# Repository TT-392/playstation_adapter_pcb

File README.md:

# RP2040 PlayStation adapter
This project is a simple PlayStation 1/2 controller port to USB C adapter. I made it so that I would be able to use it with the cheap, second hand, PlayStation 2, Taiko no Tatsujin drum, which I bought while in Japan.

I only wrote software for the Taiko drum, but in theory, all of the hardware is there to support a lot of different kinds of PlayStation controllers. The firmware can be found [here](https://github.com/TT-392/playstation_adapter_code).

## Using the hardware with non Taiko drum controllers
If you want to use this hardware with other PlayStation controllers, you are going to have to write your own firmware. For details on how to do this, I recommend the following source: [Interfacing a PS2 (PlayStation 2) Controller](https://store.curiousinventor.com/guides/PS2/).

One thing to keep in mind is power requirements of the controller you are using. I haven't found much information on how much power controllers pull (not that I put in that much effort), except for what is mentioned in the aforementioned source. Therefore, I can only give information on the power supply situation of this PCB.
* Pin 5 (power). This pin gets 3.3V through an AMS1117-3.3 voltage regulator. This voltage regulator is rated for 1A (though, this does assume that it is able to get rid of the heat), but that does assume that your USB port is able to supply that. Therefore, its power rating is, whatever your USB port is able to deliver if that is < 1A, otherwise 1A.
* Pin 3 (vibrator power). This pin is connected to the USB port VBUS pin (5V) through a 0 ohm resistor, so it can be enabled or disabled by placing or not placing that resistor. I don't know how this pin is usually used, because I only have a Taiko drum, and that drum doesn't have a vibration motor, but it felt like a good idea to give the option to leave it unconnected in case there exists a controller which pulls too much power for a USB port with the vibration motor powered, but not without it powered (assuming the controller would even work like that).
* I referred to USB power in those last 2 points. This table on [Wikipedia](https://en.wikipedia.org/wiki/USB#Power) should help you in figuring out what that is. Keep in mind that the type-c power delivery standards need extra communication between your device and the supply, and therefore cannot be used in this case. While with the BC 1.1 and 1.2 specs, you are supposed to check if there is a resistor between the D+ and D- lines to check if you are allowed to pull that much power, this PCB doesn't have the hardware to check that, but (although it is probably a bad idea), nothing is stopping you from pulling that much from ports capable of this.

## Ordering
I used JLCPCB to order my PCBs with all of their parts already pick and placed. I used [this](https://github.com/Bouni/kicad-jlcpcb-tools) plugin to do this. However, if you just want to order the same PCBs as I did, without any modifications, you can just grab the production files from the "JLCPCB" folder, or from the "releases" tab on github. The rest of this guide assumes you have your PCBs with the SMD components fully assembled at JLCPCB (nothing is stopping you from soldering them on yourself of course).

Apart from the PCBs, you should get your hands on some PlayStation controller ports with 90 degree pins. I got mine from [AliExpress](https://www.aliexpress.com/item/32818887920.html?spm=a2g0o.order_list.order_list_main.17.45ed1802iEjUwq) (AliExpress links rot quickly, but you should be able to find something similar). And some 9 pin, 3.96mm pitch pin header, I used [these](https://www.lcsc.com/product-detail/_BOOMELE-Boom-Precision-Elec-_C10586.html) (At the time of writing, you get free shipping on LCSC, if your recently ordered something from JLCPCB). And if you want some protection for your board, get some 50mm diameter heat-shrink (I got [this](https://www.aliexpress.com/item/1005002849810793.html?spm=a2g0o.order_detail.order_detail_item.3.59a3f19cWbd98H) stuff from AliExpress, seems to work well).

## assembly
If you followed the ordering instructions, you should now have a PCB that looks something like one of these:

Because the 90 degree PlayStation ports don't quite reach to the PCB, a we need something to bridge the gap. To do this, I decided to use some 3.96mm pitch, 9 pin pin headers, sadly, I couldn't find any without a plastic tab, so I just got the ones that looked like they had a tab that was easy to remove. So that is the first step in assembly, remove this tab, like is shown in the following image:

Next, this header should be soldered to the PCB, I have found that it works best if you solder on the connector with the pins sticking out about 5 mm, and with the side of the connector that has the least plastic, pointing to the edge of the board, to allow for easier snipping later (I found out about this orientation trick in the next one I assembled, therefore the pictures have the connector rotated by 180 degrees compared to what I am saying here).

Next, we glue (I used hot glue) the connector to the bottom side of the PCB, with the pins as close as possible to the pin header's pins, like shown in the following picture

The next step is to solder these pins together, be sure to use ample solder, to make sure the pins really have a good connection.

After you have soldered these pins together, you can go ahead and use some side cutters to cut the pins of the connector on the other side of the board. The result of these two steps can be seen in the following image:

Now it is time to heat shrink our adapter for some extra protection. Cut off a decent size piece of the heat shrink, so that the adapter can sit inside, with ample space on both sides:

Now use a heat gun to shrink the heat-shrink:

Now we can cut away the excess heat-shrink (I used normal scissors, just make sure they are scissors that close well), and we have our finished adapter:

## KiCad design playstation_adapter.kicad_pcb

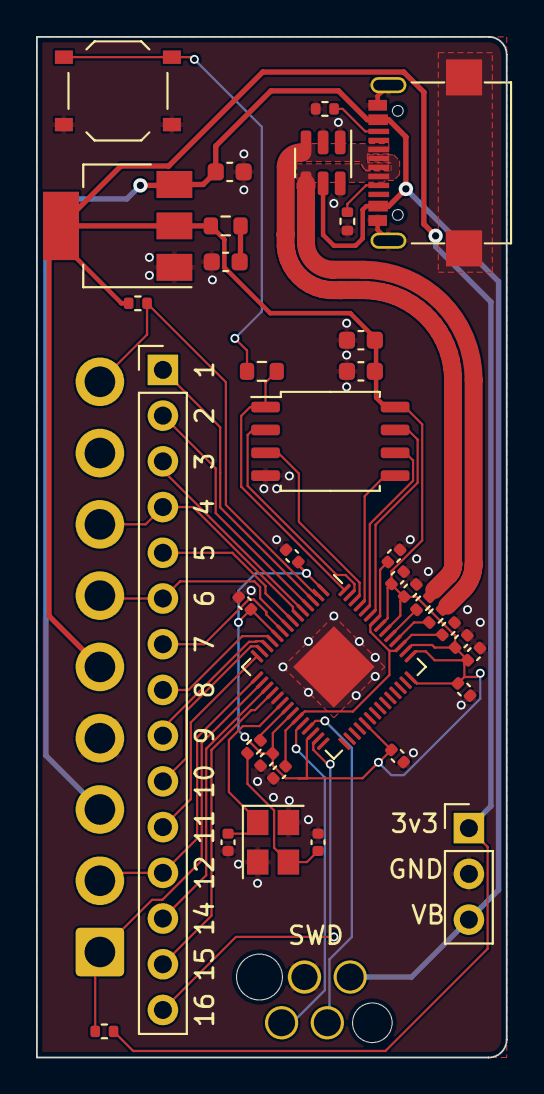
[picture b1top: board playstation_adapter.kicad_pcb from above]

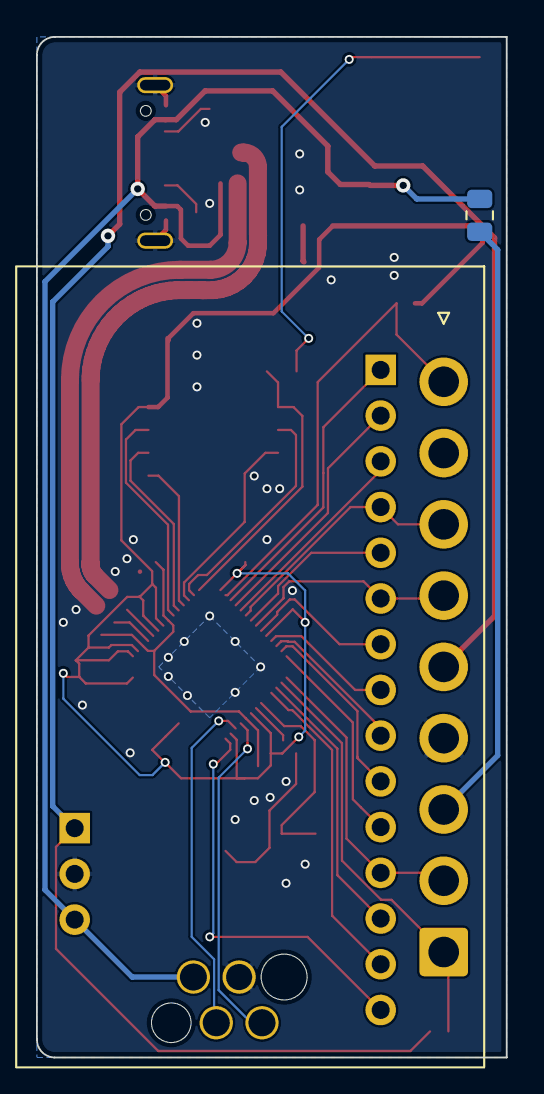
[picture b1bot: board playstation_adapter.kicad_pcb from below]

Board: 2 copper layers, 26.1 x 56.7 mm, 39 parts (2 on the bottom side), 41 nets.

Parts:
C1: 1u; C_0603_1608Metric
C2: 22u; C_0603_1608Metric
C3, C4, C5, C6, C7, C8, C9, C10, C11, C12: 100n; C_0402_1005Metric
C13, C14: 1u; C_0402_1005Metric
C15, C16: 30p; C_0402_1005Metric
C17: 100n; C_0603_1608Metric
C18: 10n; C_0603_1608Metric
J1: Conn_01x03; PinHeader_1x03_P2.54mm_Vertical
J2: Conn_01x13; PinHeader_1x15_P2.54mm_Vertical_no_courtyard
J3: GT-USB-7047C
J4: PSX port
R1: 1R; R_0603_1608Metric
R2: 0, DNF; R_0805_2012Metric
R3, R4: 27; R_0402_1005Metric
R5: 1k; R_0402_1005Metric
R6: 1k; R_0603_1608Metric
R7, R8: 5k1; R_0402_1005Metric
R9, R10: 1k5; R_0402_1005Metric
SW1: SW_Push; TS-1187A
SWD1: Conn_01x04; REDFIT 4 pin
U1: AMS1117-3.3; SOT-223-3_TabPin2_flipped_for_jlcpcb
U2: SRV05-4; SOT-23-6_flipped_for_jlcpcb
U3: RP2040; QFN-56-1EP_7x7mm_P0.4mm_EP3.2x3.2mm
U4: W25QXXXJV; SOIC-8_5.275x5.275mm_P1.27mm
Y1: X322512MSB4SI; YSX321SL, datasheet recommended measurements

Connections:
+3V3: C5.1, C6.1, C7.1, C8.1, C9.1, C10.1, C11.1, C12.1, C14.1, C17.1, C18.1, J1.1, J4.5 (pwr), R1.1, R9.1, R10.1, U1.2 (VO), U3.1 (IOVDD), U3.10 (IOVDD), U3.22 (IOVDD), U3.26 (RUN), U3.33 (IOVDD), U3.42 (IOVDD), U3.43 (ADC_AVDD), U3.44 (VREG_IN), U3.48 (USB_VDD), U3.49 (IOVDD), U4.8 (VCC)
/RP2040-base/1V1: C3.1, C4.1, C13.1, U3.23 (DVDD), U3.45 (VREG_VOUT), U3.50 (DVDD)
/RP2040-base/GPIO0: J4.9 (ack), R10.2, U3.2 (GPIO0)
/RP2040-base/GPIO1: J2.1, U3.3 (GPIO1)
/RP2040-base/GPIO2: J2.2, U3.4 (GPIO2)
/RP2040-base/GPIO3: J2.3, U3.5 (GPIO3)
/RP2040-base/GPIO4: J2.4, J4.7 (clk), U3.6 (GPIO4)
/RP2040-base/GPIO5: J2.5, U3.7 (GPIO5)
/RP2040-base/GPIO6: J2.6, J4.6 (att), U3.8 (GPIO6)
/RP2040-base/GPIO7: J2.7, U3.9 (GPIO7)
/RP2040-base/GPIO8: J2.8, U3.11 (GPIO8)
/RP2040-base/GPIO9: J2.9, U3.12 (GPIO9)
/RP2040-base/GPIO10: J2.10, U3.13 (GPIO10)
/RP2040-base/GPIO11: J2.11, U3.14 (GPIO11)
/RP2040-base/GPIO12: J2.12, J4.2 (cmd), U3.15 (GPIO12)
/RP2040-base/GPIO13: J4.1 (data), R9.2, U3.16 (GPIO13)
/RP2040-base/GPIO14: J2.13, U3.17 (GPIO14)
/RP2040-base/GPIO15: J2.14, U3.18 (GPIO15)
/RP2040-base/GPIO16: J2.15, U3.27 (GPIO16)
/RP2040-base/QSPI_SCLK: U3.52 (QSPI_SCLK), U4.6 (CLK)
/RP2040-base/QSPI_SD0: U3.53 (QSPI_SD0), U4.5 (DI(IO0))
/RP2040-base/QSPI_SD1: U3.55 (QSPI_SD1), U4.2 (DO(IO1))
/RP2040-base/QSPI_SD2: U3.54 (QSPI_SD2), U4.3 (IO2)
/RP2040-base/QSPI_SD3: U3.51 (QSPI_SD3), U4.7 (IO3)
/RP2040-base/QSPI_SS: R6.1, U3.56 (QSPI_SS), U4.1 (~CS)
/RP2040-base/SWCLK: SWD1.1, U3.24 (SWCLK)
/RP2040-base/SWD: SWD1.3, U3.25 (SWD)
/RP2040-base/USB_D+: J3.A6 (D+), J3.B6 (D+), R3.1, U2.3 (IO2)
/RP2040-base/USB_D-: J3.A7 (D-), J3.B7 (D-), R4.1, U2.4 (IO3)
/RP2040-base/XIN: C15.1, U3.20 (XIN), Y1.1
/RP2040-base/XOUT: R5.1, U3.21 (XOUT)
/RP2040-base/~USB_BOOT: R6.2, SW1.2
/vibrator power: J4.3 (vpwr), R2.2
GND: C1.2, C2.2, C3.2, C4.2, C5.2, C6.2, C7.2, C8.2, C9.2, C10.2, C11.2, C12.2, C13.2, C14.2, C15.2, C16.2, C17.2, C18.2, J1.2, J3.A1 (GND), J3.A12 (GND), J3.B1 (GND), J3.B12 (GND), J3.S1 (SHIELD), J4.4 (gnd), R7.2, R8.2, SW1.1, SWD1.2, U1.1 (GND), U2.1 (IO1), U2.2 (VN), U2.6 (IO4), U3.19 (TESTEN), U3.57 (GND), U4.4 (GND), Y1.2, Y1.4
unnamed: C2.1, R1.2
unnamed: C16.1, R5.2, Y1.3
unnamed: J3.A5 (CC1), R7.1
unnamed: J3.B5 (CC2), R8.1
unnamed: R4.2, U3.46 (USB_DM)
unnamed: R3.2, U3.47 (USB_DP)
VBUS: C1.1, J1.3, J3.A4 (VBUS), J3.A9 (VBUS), J3.B4 (VBUS), J3.B9 (VBUS), R2.1, SWD1.4, U1.3 (VI), U2.5 (VP)

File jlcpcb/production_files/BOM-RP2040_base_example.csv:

Comment,Designator,Footprint,LCSC
1k,R5,R_0402_1005Metric,C11702
100n,C17,C_0603_1608Metric,C14663
100n,"C10,C11,C12,C3,C4,C5,C6,C7,C8,C9",C_0402_1005Metric,C1525
30p,"C15,C16",C_0402_1005Metric,C1570
1u,"C1,C2",C_0603_1608Metric,C15849
RP2040,U3,QFN-56-1EP_7x7mm_P0.4mm_EP3.2x3.2mm,C2040
1k,R6,R_0603_1608Metric,C21190
27,"R3,R4",R_0402_1005Metric,C25092
5k1,"R1,R2",R_0402_1005Metric,C25905
SW_Push,SW1,TS-1187A,C318884
1u,"C13,C14",C_0402_1005Metric,C52923
XC6206P332MR,U1,SOT-23-3_flipped_for_jlcpcb,C5446
10n,C18,C_0603_1608Metric,C57112
SRV05-4,U2,SOT-23-6_flipped_for_jlcpcb,C85364
X322512MSB4SI,Y1,"YSX321SL, datasheet recommended measurements",C9002
GT-USB-7047C,J3,GT-USB-7047C,C963218
W25QXXXJV,U4,SOIC-8_5.275x5.275mm_P1.27mm,C97521
Conn_01x03,J1,PinHeader_1x03_P2.54mm_Vertical,
Conn_01x03,SWD1,PinHeader_1x03_P2.54mm_Vertical,
Conn_01x13,J2,PinHeader_1x13_P2.54mm_Vertical,

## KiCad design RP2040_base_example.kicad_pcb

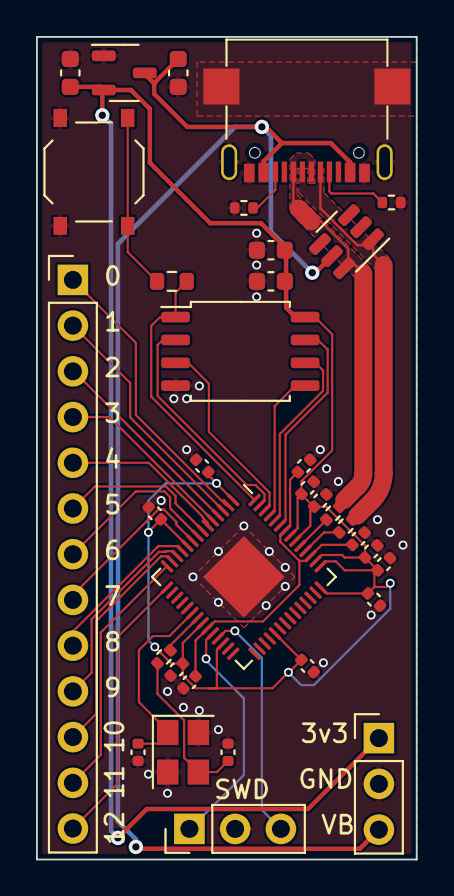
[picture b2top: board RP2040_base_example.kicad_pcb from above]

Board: 2 copper layers, 21.1 x 45.7 mm, 34 parts (0 on the bottom side), 35 nets.

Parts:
C1, C2: 1u; C_0603_1608Metric
C3, C4, C5, C6, C7, C8, C9, C10, C11, C12: 100n; C_0402_1005Metric
C13, C14: 1u; C_0402_1005Metric
C15, C16: 30p; C_0402_1005Metric
C17: 100n; C_0603_1608Metric
C18: 10n; C_0603_1608Metric
J1: Conn_01x03; PinHeader_1x03_P2.54mm_Vertical
J2: Conn_01x13; PinHeader_1x13_P2.54mm_Vertical
J3: GT-USB-7047C
R1, R2: 5k1; R_0402_1005Metric
R3, R4: 27; R_0402_1005Metric
R5: 1k; R_0402_1005Metric
R6: 1k; R_0603_1608Metric
SW1: SW_Push; TS-1187A
SWD1: Conn_01x03; PinHeader_1x03_P2.54mm_Vertical
U1: XC6206P332MR; SOT-23-3_flipped_for_jlcpcb
U2: SRV05-4; SOT-23-6_flipped_for_jlcpcb
U3: RP2040; QFN-56-1EP_7x7mm_P0.4mm_EP3.2x3.2mm
Ur: W25QXXXJV; SOIC-8_5.275x5.275mm_P1.27mm
Y1: X322512MSB4SI; YSX321SL, datasheet recommended measurements

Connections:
+3V3: C2.1, C5.1, C6.1, C7.1, C8.1, C9.1, C10.1, C11.1, C12.1, C14.1, C17.1, C18.1, J1.1, U1.2 (VO), U3.1 (IOVDD), U3.10 (IOVDD), U3.22 (IOVDD), U3.26 (RUN), U3.33 (IOVDD), U3.42 (IOVDD), U3.43 (ADC_AVDD), U3.44 (VREG_IN), U3.48 (USB_VDD), U3.49 (IOVDD), Ur.8 (VCC)
/RP2040-base/1V1: C3.1, C4.1, C13.1, U3.23 (DVDD), U3.45 (VREG_VOUT), U3.50 (DVDD)
/RP2040-base/GPIO0: J2.1, U3.2 (GPIO0)
/RP2040-base/GPIO1: J2.2, U3.3 (GPIO1)
/RP2040-base/GPIO2: J2.3, U3.4 (GPIO2)
/RP2040-base/GPIO3: J2.4, U3.5 (GPIO3)
/RP2040-base/GPIO4: J2.5, U3.6 (GPIO4)
/RP2040-base/GPIO5: J2.6, U3.7 (GPIO5)
/RP2040-base/GPIO6: J2.7, U3.8 (GPIO6)
/RP2040-base/GPIO7: J2.8, U3.9 (GPIO7)
/RP2040-base/GPIO8: J2.9, U3.11 (GPIO8)
/RP2040-base/GPIO9: J2.10, U3.12 (GPIO9)
/RP2040-base/GPIO10: J2.11, U3.13 (GPIO10)
/RP2040-base/GPIO11: J2.12, U3.14 (GPIO11)
/RP2040-base/GPIO12: J2.13, U3.15 (GPIO12)
/RP2040-base/QSPI_SCLK: U3.52 (QSPI_SCLK), Ur.6 (CLK)
/RP2040-base/QSPI_SD0: U3.53 (QSPI_SD0), Ur.5 (DI(IO0))
/RP2040-base/QSPI_SD1: U3.55 (QSPI_SD1), Ur.2 (DO(IO1))
/RP2040-base/QSPI_SD2: U3.54 (QSPI_SD2), Ur.3 (IO2)
/RP2040-base/QSPI_SD3: U3.51 (QSPI_SD3), Ur.7 (IO3)
/RP2040-base/QSPI_SS: R6.1, U3.56 (QSPI_SS), Ur.1 (~CS)
/RP2040-base/SWCLK: SWD1.1, U3.24 (SWCLK)
/RP2040-base/SWD: SWD1.3, U3.25 (SWD)
/RP2040-base/USB_D+: J3.A6 (D+), J3.B6 (D+), R3.1, U2.6 (IO4)
/RP2040-base/USB_D-: J3.A7 (D-), J3.B7 (D-), R4.1, U2.1 (IO1)
/RP2040-base/XIN: C15.1, U3.20 (XIN), Y1.1
/RP2040-base/XOUT: R5.1, U3.21 (XOUT)
/RP2040-base/~USB_BOOT: R6.2, SW1.2
GND: C1.2, C2.2, C3.2, C4.2, C5.2, C6.2, C7.2, C8.2, C9.2, C10.2, C11.2, C12.2, C13.2, C14.2, C15.2, C16.2, C17.2, C18.2, J1.2, J3.A1 (GND), J3.A12 (GND), J3.B1 (GND), J3.B12 (GND), J3.S1 (SHIELD), R1.2, R2.2, SW1.1, SWD1.2, U1.1 (GND), U2.2 (VN), U2.3 (IO2), U2.4 (IO3), U3.19 (TESTEN), U3.57 (GND), Ur.4 (GND), Y1.2, Y1.4
unnamed: C16.1, R5.2, Y1.3
unnamed: J3.A5 (CC1), R1.1
unnamed: J3.B5 (CC2), R2.1
unnamed: R4.2, U3.46 (USB_DM)
unnamed: R3.2, U3.47 (USB_DP)
VBUS: C1.1, J1.3, J3.A4 (VBUS), J3.A9 (VBUS), J3.B4 (VBUS), J3.B9 (VBUS), U1.3 (VI), U2.5 (VP)

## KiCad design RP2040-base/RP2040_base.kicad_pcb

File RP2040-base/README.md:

# RP2040-base
Basic drop in RP2040 kicad schematic sheet

# IMPORTANT
Not quite ready for use yet, for details, see notes.md.

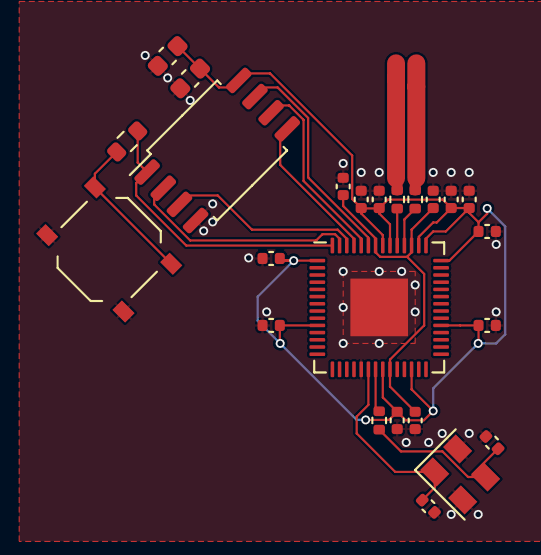
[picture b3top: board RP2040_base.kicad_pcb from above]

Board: 2 copper layers, 24 parts (0 on the bottom side), 15 nets.

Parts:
C1, C2, C3, C4, C5, C8, C9, C18, C19, C28: 100n; C_0402_1005Metric
C6, C7: 1u; C_0402_1005Metric
C29: 100n; C_0603_1608Metric
C30: 10n; C_0603_1608Metric
C31, C32: 30p; C_0402_1005Metric
R6, R7: 27; R_0402_1005Metric
R8: 1k; R_0603_1608Metric
R10: 1k; R_0402_1005Metric
SW1: SW_Push; TS-1187A
U1: W25Q16JV; SOIC-8_5.275x5.275mm_P1.27mm
U2: RP2040; QFN-56-1EP_7x7mm_P0.4mm_EP3.2x3.2mm
Y2: ECS-120-8-33-JGN-TR3; Crystal_SMD_EuroQuartz_MT-4Pin_3.2x2.5mm

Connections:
/1V1: C6.1, C18.1, C19.1, U2.23 (DVDD), U2.45 (VREG_VOUT), U2.50 (DVDD)
/GND: C1.2, C2.2, C3.2, C4.2, C5.2, C6.2, C7.2, C8.2, C9.2, C18.2, C19.2, C28.2, C29.2, C30.2, C31.2, C32.2, SW1.1, U1.4 (GND), U2.19 (TESTEN), U2.57 (GND), Y2.2, Y2.4
/QSPI_SCLK: U1.6 (CLK), U2.52 (QSPI_SCLK)
/QSPI_SD0: U1.5 (DI(IO0)), U2.53 (QSPI_SD0)
/QSPI_SD1: U1.2 (DO(IO1)), U2.55 (QSPI_SD1)
/QSPI_SD2: U1.3 (IO2), U2.54 (QSPI_SD2)
/QSPI_SD3: U1.7 (IO3), U2.51 (QSPI_SD3)
/QSPI_SS: R8.1, U1.1 (~CS), U2.56 (QSPI_SS)
/VIN: C1.1, C2.1, C3.1, C4.1, C5.1, C7.1, C8.1, C9.1, C28.1, C29.1, C30.1, U1.8 (VCC), U2.1 (IOVDD), U2.10 (IOVDD), U2.22 (IOVDD), U2.26 (RUN), U2.33 (IOVDD), U2.42 (IOVDD), U2.43 (ADC_AVDD), U2.44 (VREG_IN), U2.48 (USB_VDD), U2.49 (IOVDD)
/XIN: C31.1, U2.20 (XIN), Y2.1
/XOUT: R10.1, U2.21 (XOUT)
/~USB_BOOT: R8.2, SW1.2
unnamed: C32.1, R10.2, Y2.3
unnamed: R7.2, U2.46 (USB_DM)
unnamed: R6.2, U2.47 (USB_DP)

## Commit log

2023-07-22 Rev 0.1
2023-07-22 Create LICENSE
2023-07-22 Add git url
2023-07-28 Create sample pcb layout, manage schematic files better, and fill in missing 3d model.
2023-07-28 Fix some bugs in RP2040-base
2023-07-28 Add second path to 3d model, one directory deeper, to allow for the model to be used from a project in a lower directory.
2023-07-28 Fix GPIO29_ADC3 pin name
2023-07-28 Expose pins through bus instead
2023-07-29 Finish schematic
2023-07-29 Reannotate
2023-07-30 Add bugs and improvement notes
2023-07-30 Swap crystal
2023-07-30 Complete pcb + jlcpcb production files for part placement test on website
2023-07-30 Add termination resistor note
2023-07-30 Rotate footprints to coincide with jlcpcb rotation
2023-07-30 Add title blocks, and set version to 0.9 (will bump to 1.0 if ordered and tested)
2023-07-30 Fix date
2023-07-30 Add license info
2023-07-30 Rename project and modify license
2023-08-01 Modified example pcb to playstation adapter pcb
2023-08-29 Bump version number after having ordered and tested pcb
2023-08-30 Add documentation
